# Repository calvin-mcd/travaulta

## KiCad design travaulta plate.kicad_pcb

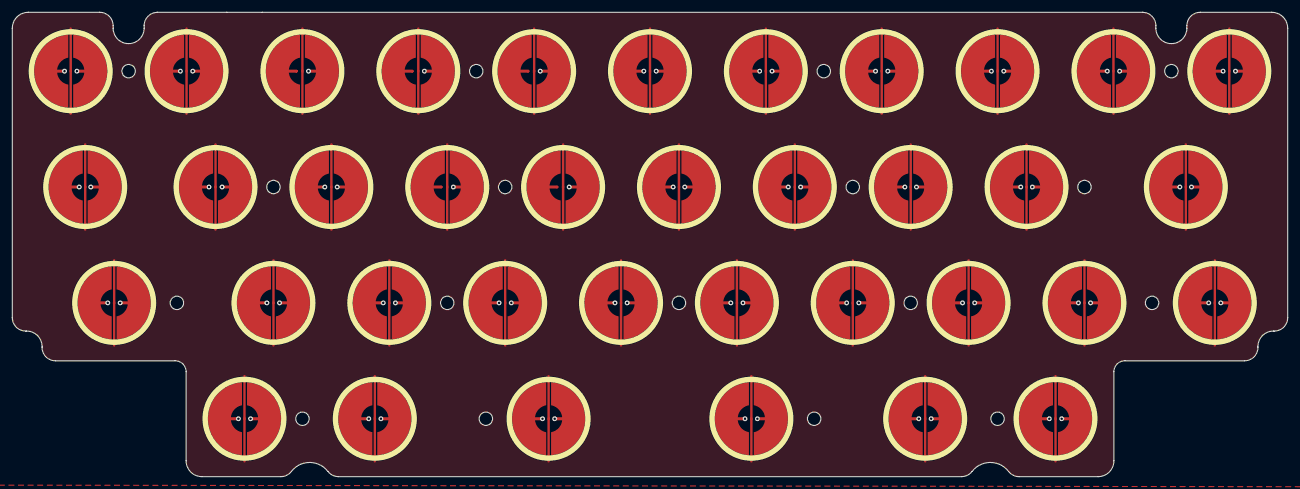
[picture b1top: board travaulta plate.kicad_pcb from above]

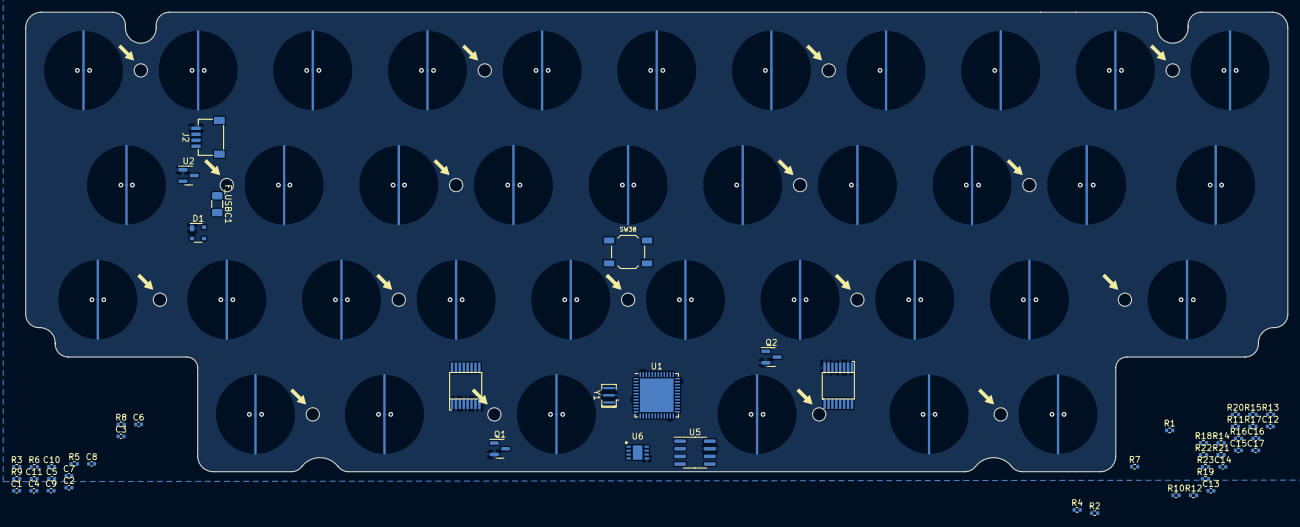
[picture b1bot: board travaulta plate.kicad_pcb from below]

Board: 4 copper layers, 209.7 x 76.4 mm, 116 parts (53 on the bottom side), 46 nets.

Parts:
C1, C2: 4.7u; C_0402_1005Metric
C3, C4, C5, C11, C17: 1u; C_0402_1005Metric
C6, C7, C8, C9, C10: 100n; C_0402_1005Metric
C12, C13, C15, C16: 0.1u; C_0402_1005Metric
C14: 220p; C_0402_1005Metric
D1: PRTR5V0U2X; SOT-143
F_USBC1: 500mA; Fuse_1206_3216Metric
H1, H2, H3, H4, H5, H6, H7, H8, H9, H10, H11, H12, H13, H14, H15, H16, H17, H18, H19, H20, H21, H22, H23, H24, H25, H26: MountingHole; HOLE_M2
J2: JST; JST-SR-4
Q1, Q2: 2N7002; SOT-23
R1, R2, R8, R9, R21: 100; R_0402_1005Metric
R3, R6, R7: 10k; R_0402_1005Metric
R4, R5, R10, R11, R12, R13, R14, R15, R16, R17, R18, R19, R20, R22: 100k; R_0402_1005Metric
R23: 1k; R_0402_1005Metric
SW1, SW2, SW3, SW4, SW5, SW6, SW7, SW8, SW9, SW10, SW11, SW12, SW13, SW14, SW15, SW16, SW17, SW18, SW19, SW20, SW21, SW22, SW23, SW24, SW25, SW26, SW27, SW28, SW29, SW30, SW31, SW32, SW33, SW34, SW35, SW36, SW37: EC_SW; ecs_pad_1U_no_ring
SW38: SW_MEC_5G; SW_SPST_TL3342
U1: STM32F411CCUx; QFN-48-1EP_7x7mm_P0.5mm_EP5.6x5.6mm
U2: XC6206PxxxMR; SOT-23
U3, U4: 74HC4051; TSSOP16
U5: OPA350; SOIC-8_3.9x4.9mm_P1.27mm
U6: MAX5423
Y1: 16 MHz; Resonator_SMD_Murata_CSTxExxV-3Pin_3.0x1.1mm

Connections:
+5V: C4.1, F_USBC1.2, U2.3 (VI)
ADC: U1.13 (PA3), U5.6 (OUT), U6.6 (L)
AMUX_SEL_0: U1.43 (PB7), U3.11 (S0), U4.11 (S0)
AMUX_SEL_1: U1.42 (PB6), U3.10 (S1), U4.10 (S1)
AMUX_SEL_2: U1.41 (PB5), U3.9 (S2), U4.9 (S2)
APLEX_EN_PIN_0: U1.46 (PB9), U4.6 (~E)
APLEX_EN_PIN_1: U1.45 (PB8), U3.6 (~E)
APLEX_OUT_PIN_0: C14.2, Q2.3 (D), U3.3 (A), U4.3 (A), U5.2 (IN-)
BOOT0: C2.1, R3.1, SW38.1 (A), SW38.2 (A), U1.44 (BOOT0)
BOOT1: R7.2, U1.20 (PB2)
COL0: R11.1, SW1.2, SW12.2, SW22.2, U4.13 (A0)
COL1: R13.1, SW2.2, SW13.2, SW23.2, SW32.2, U4.14 (A1)
COL2: R15.1, SW3.2, SW14.2, SW24.2, SW33.2, U4.15 (A2)
COL3: R17.1, SW4.2, SW15.2, SW25.2, SW34.2, U4.12 (A3)
COL4: R19.1, SW5.2, SW16.2, SW26.2, U4.1 (A4)
COL5: R20.1, SW6.2, SW17.2, SW27.2, SW35.2, U4.5 (A5)
COL6: R10.1, SW7.2, SW18.2, SW28.2, U3.13 (A0)
COL7: R12.1, SW8.2, SW19.2, SW29.2, SW36.2, U3.14 (A1)
COL8: R14.1, SW9.2, SW20.2, SW30.2, SW37.2, U3.15 (A2)
COL9: R16.1, SW10.2, SW21.2, SW31.2, U3.12 (A3)
COL10: R18.1, SW11.2, U3.1 (A4)
D+: D1.3 (I/O2), J2.3, U1.33 (PA12)
D-: D1.2 (I/O1), J2.2, U1.32 (PA11)
DISCHARGE_PIN: R21.1, U1.18 (PB0)
GND: C1.2, C3.2, C4.2, C5.2, C6.2, C7.2, C8.2, C9.2, C10.2, C11.2, C12.2, C13.2, C14.1, C15.2, C16.1, C17.1, D1.1 (GND), J2.4, Q1.2 (S), Q2.2 (S), R3.2, R5.2, R7.1, R10.2, R11.2, R12.2, R13.2, R14.2, R15.2, R16.2, R17.2, R18.2, R19.2, R20.2, R22.2, R23.2, SW1.3 (SG), SW2.3 (SG), SW3.3 (SG), SW4.3 (SG), SW5.3 (SG), SW6.3 (SG), SW7.3 (SG), SW8.3 (SG), SW9.3 (SG), SW10.3 (SG), SW11.3 (SG), SW12.3 (SG), SW13.3 (SG), SW14.3 (SG), SW15.3 (SG), SW16.3 (SG), SW17.3 (SG), SW18.3 (SG), SW19.3 (SG), SW20.3 (SG), SW21.3 (SG), SW22.3 (SG), SW23.3 (SG), SW24.3 (SG), SW25.3 (SG), SW26.3 (SG), SW27.3 (SG), SW28.3 (SG), SW29.3 (SG), SW30.3 (SG), SW31.3 (SG), SW32.3 (SG), SW33.3 (SG), SW34.3 (SG), SW35.3 (SG), SW36.3 (SG), SW37.3 (SG), U1.8 (VSSA), U1.23 (VSS), U1.35 (VSS), U1.47 (VSS), U1.49 (VSS), U2.1 (GND), U3.2 (A6), U3.4 (A7), U3.5 (A5), U3.7 (VEE), U3.8 (GND), U4.2 (A6), U4.4 (A7), U4.7 (VEE), U4.8 (GND), U5.7 (V+), U6.5 (Gnd), Y1.2
NRST: C3.1, Q1.3 (D), R6.2, U1.7 (NRST)
unnamed: C1.1, U1.22 (VCAP1)
unnamed: C2.2, Q1.1 (G), R5.1
unnamed: Q2.1 (G), R21.2, R22.1
unnamed: R1.1, U1.39 (PB3)
unnamed: R2.2, U1.40 (PB4)
unnamed: R4.1, U1.31 (PA10)
unnamed: R9.1, U1.38 (PA15)
RES_L: R23.1, U5.3 (IN+), U6.7 (W), U6.8 (H)
ROW0: R1.2, SW1.1, SW2.1, SW3.1, SW4.1, SW5.1, SW6.1, SW7.1, SW8.1, SW9.1, SW10.1, SW11.1
ROW1: R9.2, SW12.1, SW13.1, SW14.1, SW15.1, SW16.1, SW17.1, SW18.1, SW19.1, SW20.1, SW21.1
ROW2: R8.1, SW22.1, SW23.1, SW24.1, SW25.1, SW26.1, SW27.1, SW28.1, SW29.1, SW30.1, SW31.1
ROW3: R2.1, SW32.1, SW33.1, SW34.1, SW35.1, SW36.1, SW37.1
SPI1_CLK: U1.15 (PA5), U6.2 (SCLK)
SPI1_CS: U1.19 (PB1), U6.4 (CS)
SPI1_MOSI: U1.17 (PA7), U6.3 (Din)
SWCLK: R8.2, U1.37 (PA14)
VBAT: C5.1, C6.1, C7.1, C8.1, C9.1, C10.1, C11.1, C12.1, C13.1, C15.1, C16.2, C17.2, R4.2, R6.1, U1.1 (VBAT), U1.9 (VDDA), U1.24 (VDD), U1.36 (VDD), U1.48 (VDD), U2.2 (VO), U3.16 (VCC), U4.16 (VCC), U5.4 (V-), U6.1 (VCC)
VCC: D1.4 (VCC), F_USBC1.1, J2.1
XTAL0: U1.5 (PH0), Y1.3
XTAL1: U1.6 (PH1), Y1.1

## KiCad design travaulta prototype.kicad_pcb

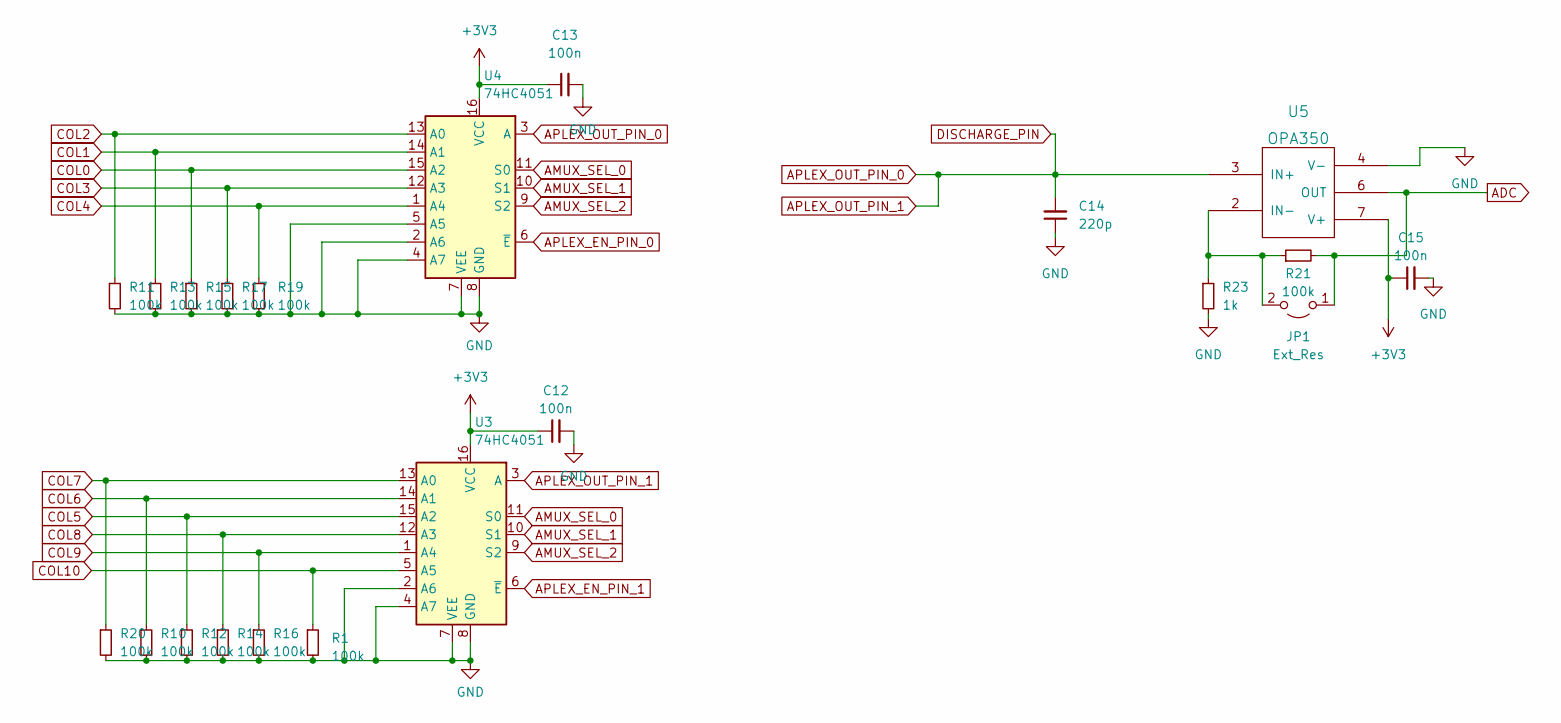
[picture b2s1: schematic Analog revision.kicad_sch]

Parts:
C12, C13, C15: 100n; C_0402_1005Metric
C14: 220p; C_0402_1005Metric
JP1: Ext_Res; R_0603_1608Metric_Pad0.98x0.95mm_HandSolder
R1, R10, R11, R12, R13, R14, R15, R16, R17, R19, R20, R21: 100k; R_0402_1005Metric
R23: 1k; R_0402_1005Metric
U3, U4: 74HC4051; TSSOP16
U5: OPA350; SOIC-8_3.9x4.9mm_P1.27mm

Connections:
ADC: JP1.1 (A), R21.2, U5.6 (OUT); also elsewhere on the board
AMUX_SEL_0: U3.11 (S0), U4.11 (S0); also elsewhere on the board
AMUX_SEL_1: U3.10 (S1), U4.10 (S1); also elsewhere on the board
AMUX_SEL_2: U3.9 (S2), U4.9 (S2); also elsewhere on the board
APLEX_EN_PIN_0: U4.6 (~E); also elsewhere on the board
APLEX_EN_PIN_1: U3.6 (~E); also elsewhere on the board
APLEX_OUT_PIN_0: C14.2, U3.3 (A), U4.3 (A), U5.3 (IN+); also elsewhere on the board
COL0: R15.1, U4.15 (A2); also elsewhere on the board
COL1: R13.1, U4.14 (A1); also elsewhere on the board
COL2: R11.1, U4.13 (A0); also elsewhere on the board
COL3: R17.1, U4.12 (A3); also elsewhere on the board
COL4: R19.1, U4.1 (A4); also elsewhere on the board
COL5: R12.1, U3.15 (A2); also elsewhere on the board
COL6: R10.1, U3.14 (A1); also elsewhere on the board
COL7: R20.1, U3.13 (A0); also elsewhere on the board
COL8: R14.1, U3.12 (A3); also elsewhere on the board
COL9: R16.1, U3.1 (A4); also elsewhere on the board
unnamed: JP1.2 (B), R21.1, R23.1, U5.2 (IN-)

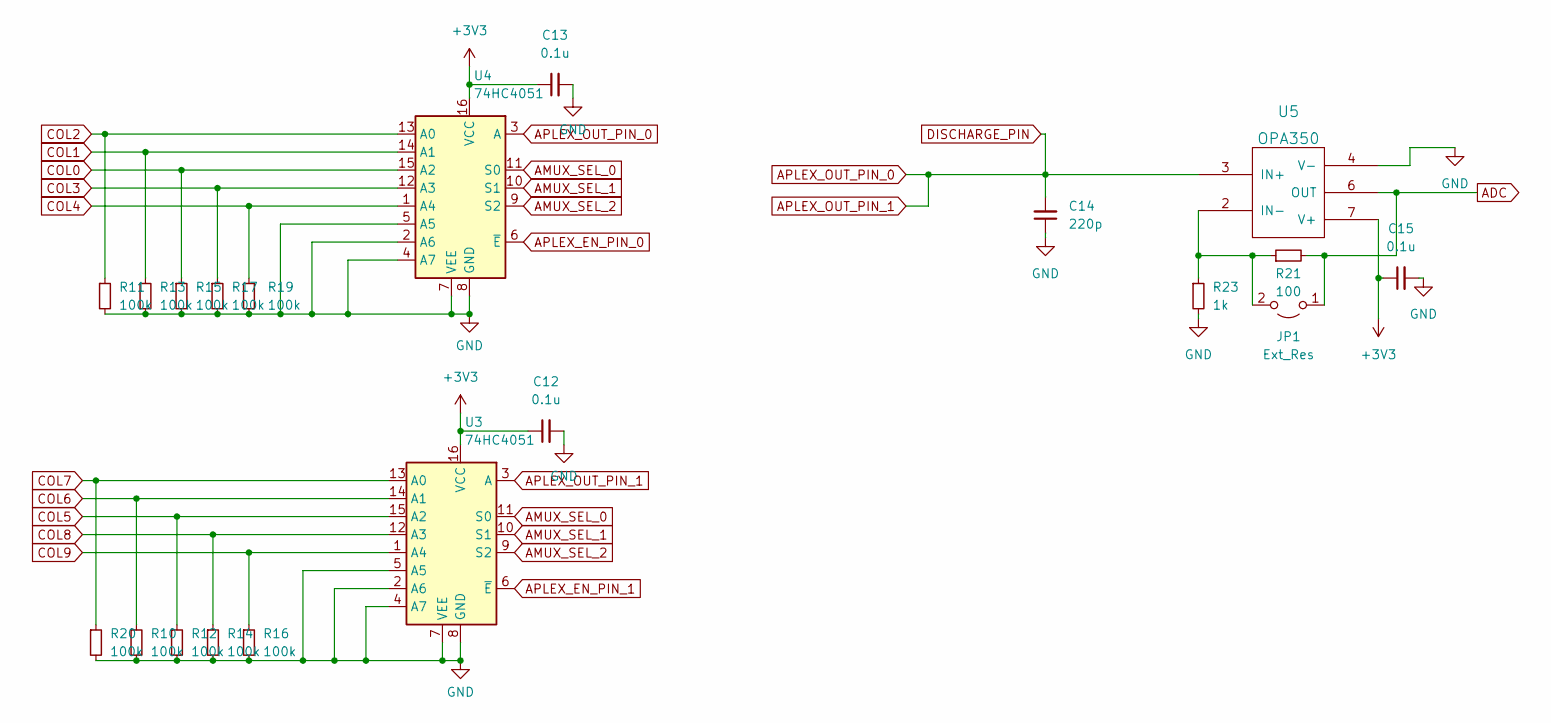
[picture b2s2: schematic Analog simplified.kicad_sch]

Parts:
C12, C13, C15: 0.1u; C_0402_1005Metric
C14: 220p; C_0402_1005Metric
JP1: Ext_Res; R_0603_1608Metric_Pad0.98x0.95mm_HandSolder
R10, R11, R12, R13, R14, R15, R16, R17, R19, R20: 100k; R_0402_1005Metric
R21: 100; R_0402_1005Metric
R23: 1k; R_0402_1005Metric
U3, U4: 74HC4051; TSSOP16
U5: OPA350; SOIC-8_3.9x4.9mm_P1.27mm

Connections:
ADC: JP1.1 (A), R21.2, U5.6 (OUT); also elsewhere on the board
AMUX_SEL_0: U3.11 (S0), U4.11 (S0); also elsewhere on the board
AMUX_SEL_1: U3.10 (S1), U4.10 (S1); also elsewhere on the board
AMUX_SEL_2: U3.9 (S2), U4.9 (S2); also elsewhere on the board
APLEX_EN_PIN_0: U4.6 (~E); also elsewhere on the board
APLEX_EN_PIN_1: U3.6 (~E); also elsewhere on the board
APLEX_OUT_PIN_0: C14.2, U3.3 (A), U4.3 (A), U5.3 (IN+); also elsewhere on the board
COL0: R15.1, U4.15 (A2); also elsewhere on the board
COL1: R13.1, U4.14 (A1); also elsewhere on the board
COL2: R11.1, U4.13 (A0); also elsewhere on the board
COL3: R17.1, U4.12 (A3); also elsewhere on the board
COL4: R19.1, U4.1 (A4); also elsewhere on the board
COL5: R12.1, U3.15 (A2); also elsewhere on the board
COL6: R10.1, U3.14 (A1); also elsewhere on the board
COL7: R20.1, U3.13 (A0); also elsewhere on the board
COL8: R14.1, U3.12 (A3); also elsewhere on the board
COL9: R16.1, U3.1 (A4); also elsewhere on the board
unnamed: JP1.2 (B), R21.1, R23.1, U5.2 (IN-)

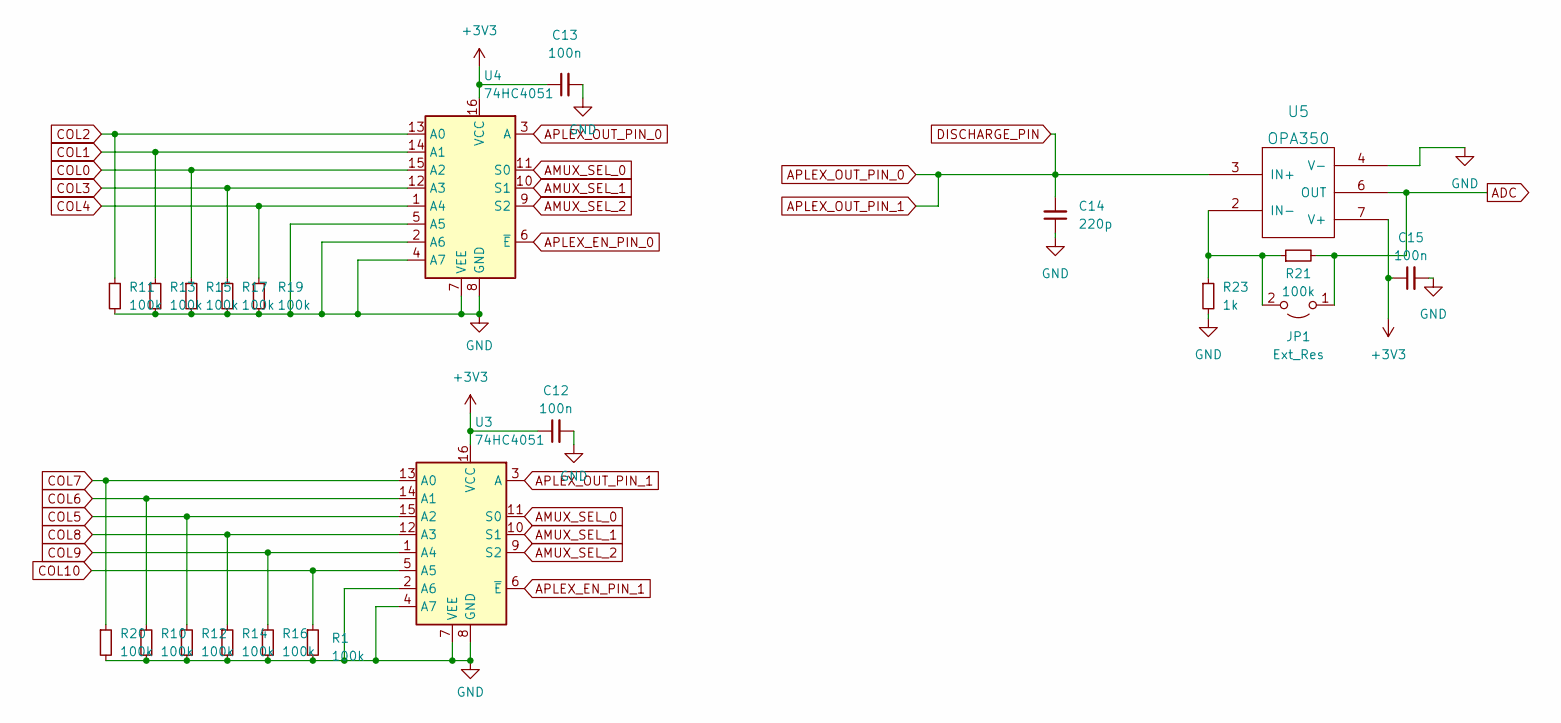
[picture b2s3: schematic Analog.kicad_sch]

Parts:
C12, C13, C15: 100n; C_0402_1005Metric
C14: 220p; C_0402_1005Metric
JP1: Ext_Res; R_0603_1608Metric_Pad0.98x0.95mm_HandSolder
R1, R10, R11, R12, R13, R14, R15, R16, R17, R19, R20, R21: 100k; R_0402_1005Metric
R23: 1k; R_0402_1005Metric
U3, U4: 74HC4051; TSSOP16
U5: OPA350; SOIC-8_3.9x4.9mm_P1.27mm

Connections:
ADC: JP1.1 (A), R21.2, U5.6 (OUT); also elsewhere on the board
AMUX_SEL_0: U3.11 (S0), U4.11 (S0); also elsewhere on the board
AMUX_SEL_1: U3.10 (S1), U4.10 (S1); also elsewhere on the board
AMUX_SEL_2: U3.9 (S2), U4.9 (S2); also elsewhere on the board
APLEX_EN_PIN_0: U4.6 (~E); also elsewhere on the board
APLEX_EN_PIN_1: U3.6 (~E); also elsewhere on the board
APLEX_OUT_PIN_0: C14.2, U3.3 (A), U4.3 (A), U5.3 (IN+); also elsewhere on the board
COL0: R15.1, U4.15 (A2); also elsewhere on the board
COL1: R13.1, U4.14 (A1); also elsewhere on the board
COL2: R11.1, U4.13 (A0); also elsewhere on the board
COL3: R17.1, U4.12 (A3); also elsewhere on the board
COL4: R19.1, U4.1 (A4); also elsewhere on the board
COL5: R12.1, U3.15 (A2); also elsewhere on the board
COL6: R10.1, U3.14 (A1); also elsewhere on the board
COL7: R20.1, U3.13 (A0); also elsewhere on the board
COL8: R14.1, U3.12 (A3); also elsewhere on the board
COL9: R16.1, U3.1 (A4); also elsewhere on the board
unnamed: JP1.2 (B), R21.1, R23.1, U5.2 (IN-)

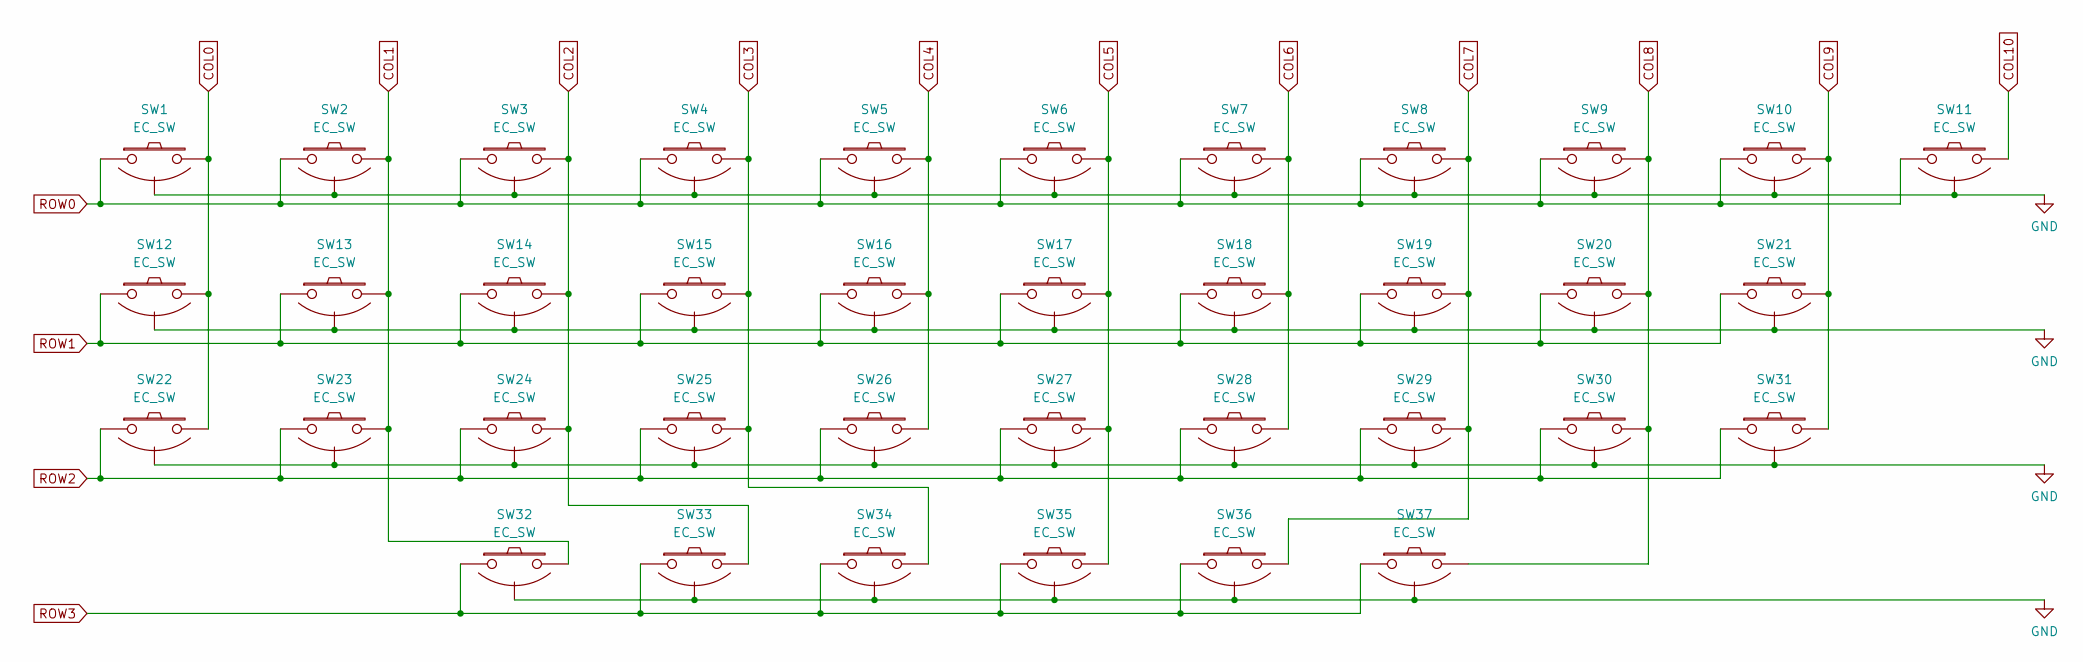
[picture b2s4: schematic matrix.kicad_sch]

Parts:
SW1, SW2, SW3, SW4, SW5, SW6, SW7, SW8, SW9, SW10, SW11, SW12, SW13, SW14, SW15, SW16, SW17, SW18, SW19, SW20, SW21, SW22, SW23, SW24, SW25, SW26, SW27, SW28, SW29, SW30, SW31, SW32, SW33, SW34, SW35, SW36, SW37: EC_SW; ecs_pad_1U_no_ring

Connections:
COL0: SW1.2, SW12.2, SW22.2; also elsewhere on the board
COL1: SW2.2, SW13.2, SW23.2, SW32.2; also elsewhere on the board
COL2: SW3.2, SW14.2, SW24.2, SW33.2; also elsewhere on the board
COL3: SW4.2, SW15.2, SW25.2, SW34.2; also elsewhere on the board
COL4: SW5.2, SW16.2, SW26.2; also elsewhere on the board
COL5: SW6.2, SW17.2, SW27.2, SW35.2; also elsewhere on the board
COL6: SW7.2, SW18.2, SW28.2; also elsewhere on the board
COL7: SW8.2, SW19.2, SW29.2, SW36.2; also elsewhere on the board
COL8: SW9.2, SW20.2, SW30.2, SW37.2; also elsewhere on the board
COL9: SW10.2, SW21.2, SW31.2; also elsewhere on the board
ROW0: SW1.1, SW2.1, SW3.1, SW4.1, SW5.1, SW6.1, SW7.1, SW8.1, SW9.1, SW10.1, SW11.1; also elsewhere on the board
ROW1: SW12.1, SW13.1, SW14.1, SW15.1, SW16.1, SW17.1, SW18.1, SW19.1, SW20.1, SW21.1; also elsewhere on the board
ROW2: SW22.1, SW23.1, SW24.1, SW25.1, SW26.1, SW27.1, SW28.1, SW29.1, SW30.1, SW31.1; also elsewhere on the board

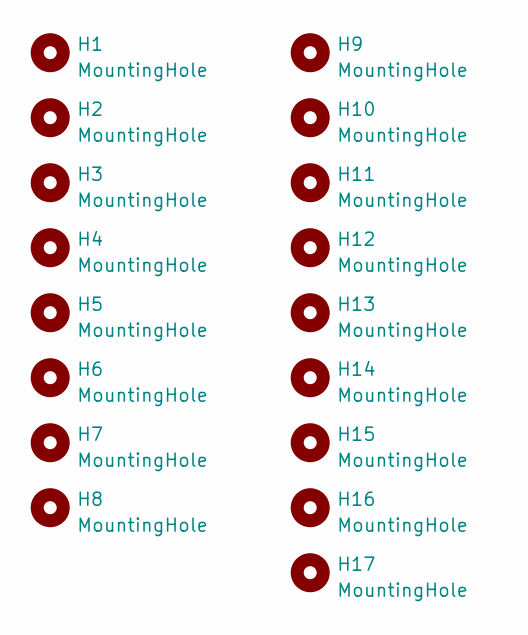
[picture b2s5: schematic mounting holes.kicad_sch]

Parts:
H1, H2, H3, H4, H5, H6, H7, H8, H9, H10, H11, H12, H13, H14, H15, H16, H17: MountingHole; HOLE_M2

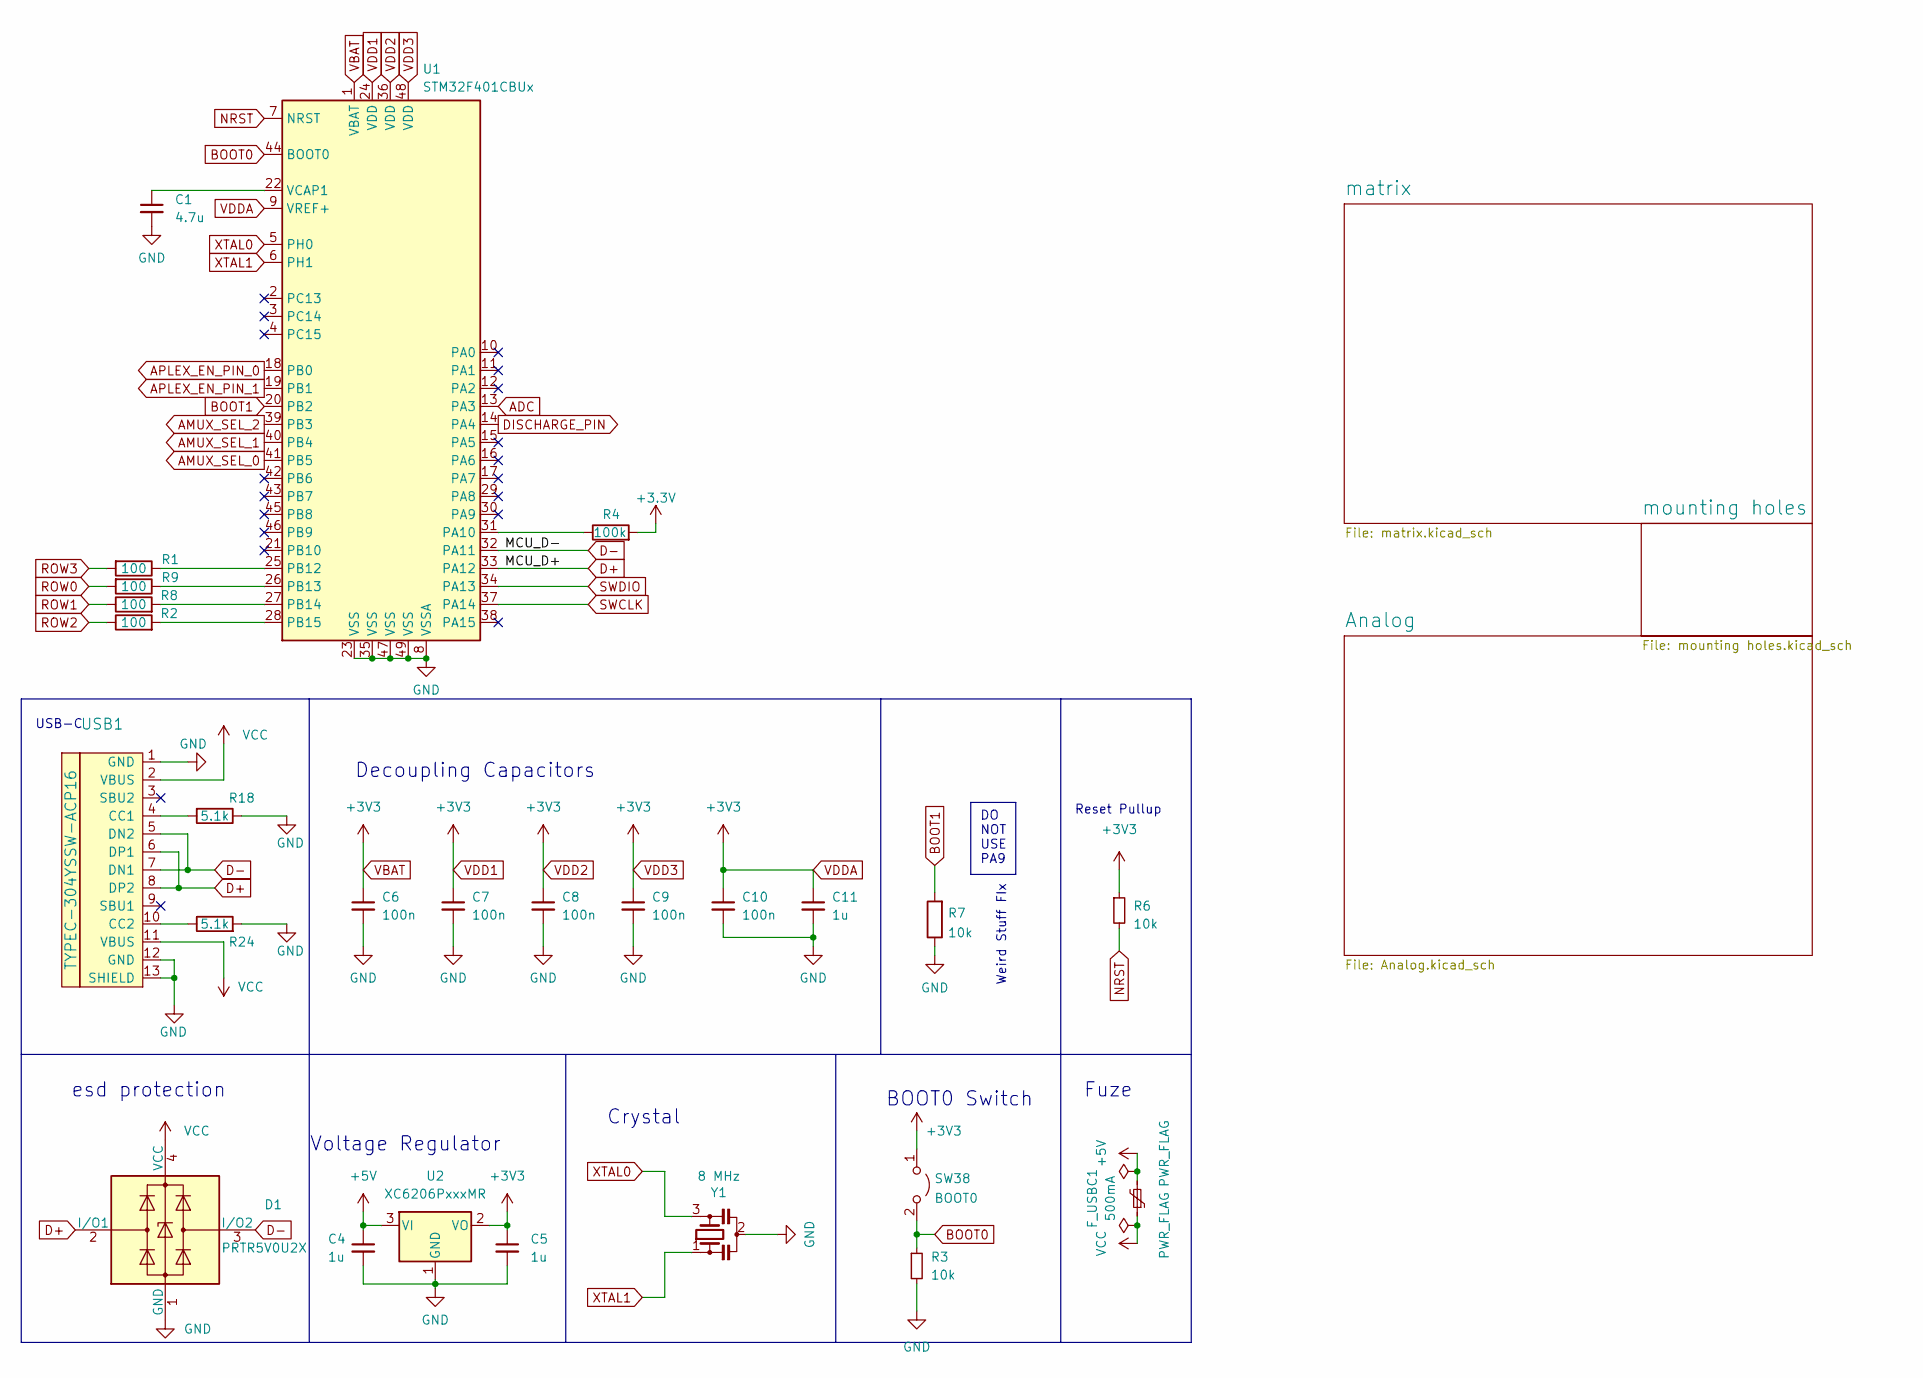
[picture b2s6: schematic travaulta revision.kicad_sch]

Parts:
C1: 4.7u; C_0402_1005Metric
C4, C5, C11: 1u; C_0402_1005Metric
C6, C7, C8, C9, C10: 100n; C_0402_1005Metric
D1: PRTR5V0U2X; SOT-143
F_USBC1: 500mA; Fuse_1206_3216Metric
R1, R2, R8, R9: 100; R_0402_1005Metric; LCSC C25076
R3, R6: 10k; R_0402_1005Metric
R4: 100k; R_0402_1005Metric; LCSC C25741
R7: 10k; R_0402_1005Metric; LCSC C25744
R18, R24: 5.1k; R_0402_1005Metric; LCSC C25905
SW38: BOOT0; PinHeader_1x02_P2.54mm_Vertical
U1: STM32F401CBUx; QFN-48-1EP_7x7mm_P0.5mm_EP5.6x5.6mm; LCSC C118825
U2: XC6206PxxxMR; SOT-23
USB1: TYPEC-304YSSW-ACP16; LCSC C2840392
Y1: 8 MHz; Resonator_SMD_Murata_CSTxExxV-3Pin_3.0x1.1mm; LCSC C907975

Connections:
+5V: C4.1, F_USBC1.2, U2.3 (VI)
ADC: U1.13 (PA3); also elsewhere on the board
AMUX_SEL_0: U1.41 (PB5); also elsewhere on the board
AMUX_SEL_1: U1.40 (PB4); also elsewhere on the board
AMUX_SEL_2: U1.39 (PB3); also elsewhere on the board
APLEX_EN_PIN_0: U1.18 (PB0); also elsewhere on the board
APLEX_EN_PIN_1: U1.19 (PB1); also elsewhere on the board
APLEX_OUT_PIN_0: U1.14 (PA4); also elsewhere on the board
BOOT0: R3.1, SW38.2 (B), U1.44 (BOOT0)
BOOT1: R7.2, U1.20 (PB2)
D+: D1.2 (I/O1), U1.33 (PA12), USB1.6 (DP1), USB1.8 (DP2)
D-: D1.3 (I/O2), U1.32 (PA11), USB1.5 (DN2), USB1.7 (DN1)
NRST: R6.2, U1.7 (NRST)
unnamed: R4.1, U1.31 (PA10)
unnamed: R9.1, U1.26 (PB13)
unnamed: R8.2, U1.27 (PB14)
unnamed: R2.2, U1.28 (PB15)
unnamed: C1.1, U1.22 (VCAP1)
unnamed: R18.2, USB1.4 (CC1)
unnamed: R24.1, USB1.10 (CC2)
ROW0: R9.2; also elsewhere on the board
ROW1: R8.1; also elsewhere on the board
ROW2: R2.1; also elsewhere on the board
SWCLK: U1.37 (PA14)
SWDIO: U1.34 (PA13)
VCC: D1.4 (VCC), F_USBC1.1, USB1.2 (VBUS), USB1.11 (VBUS)
XTAL0: U1.5 (PH0), Y1.3
XTAL1: U1.6 (PH1), Y1.1

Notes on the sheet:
Weird Stuff FIx
BOOT0 Switch
USB-C
Voltage Regulator
Reset Pullup
esd protection
DO NOT USE PA9
Fuze
Crystal
Decoupling Capacitors

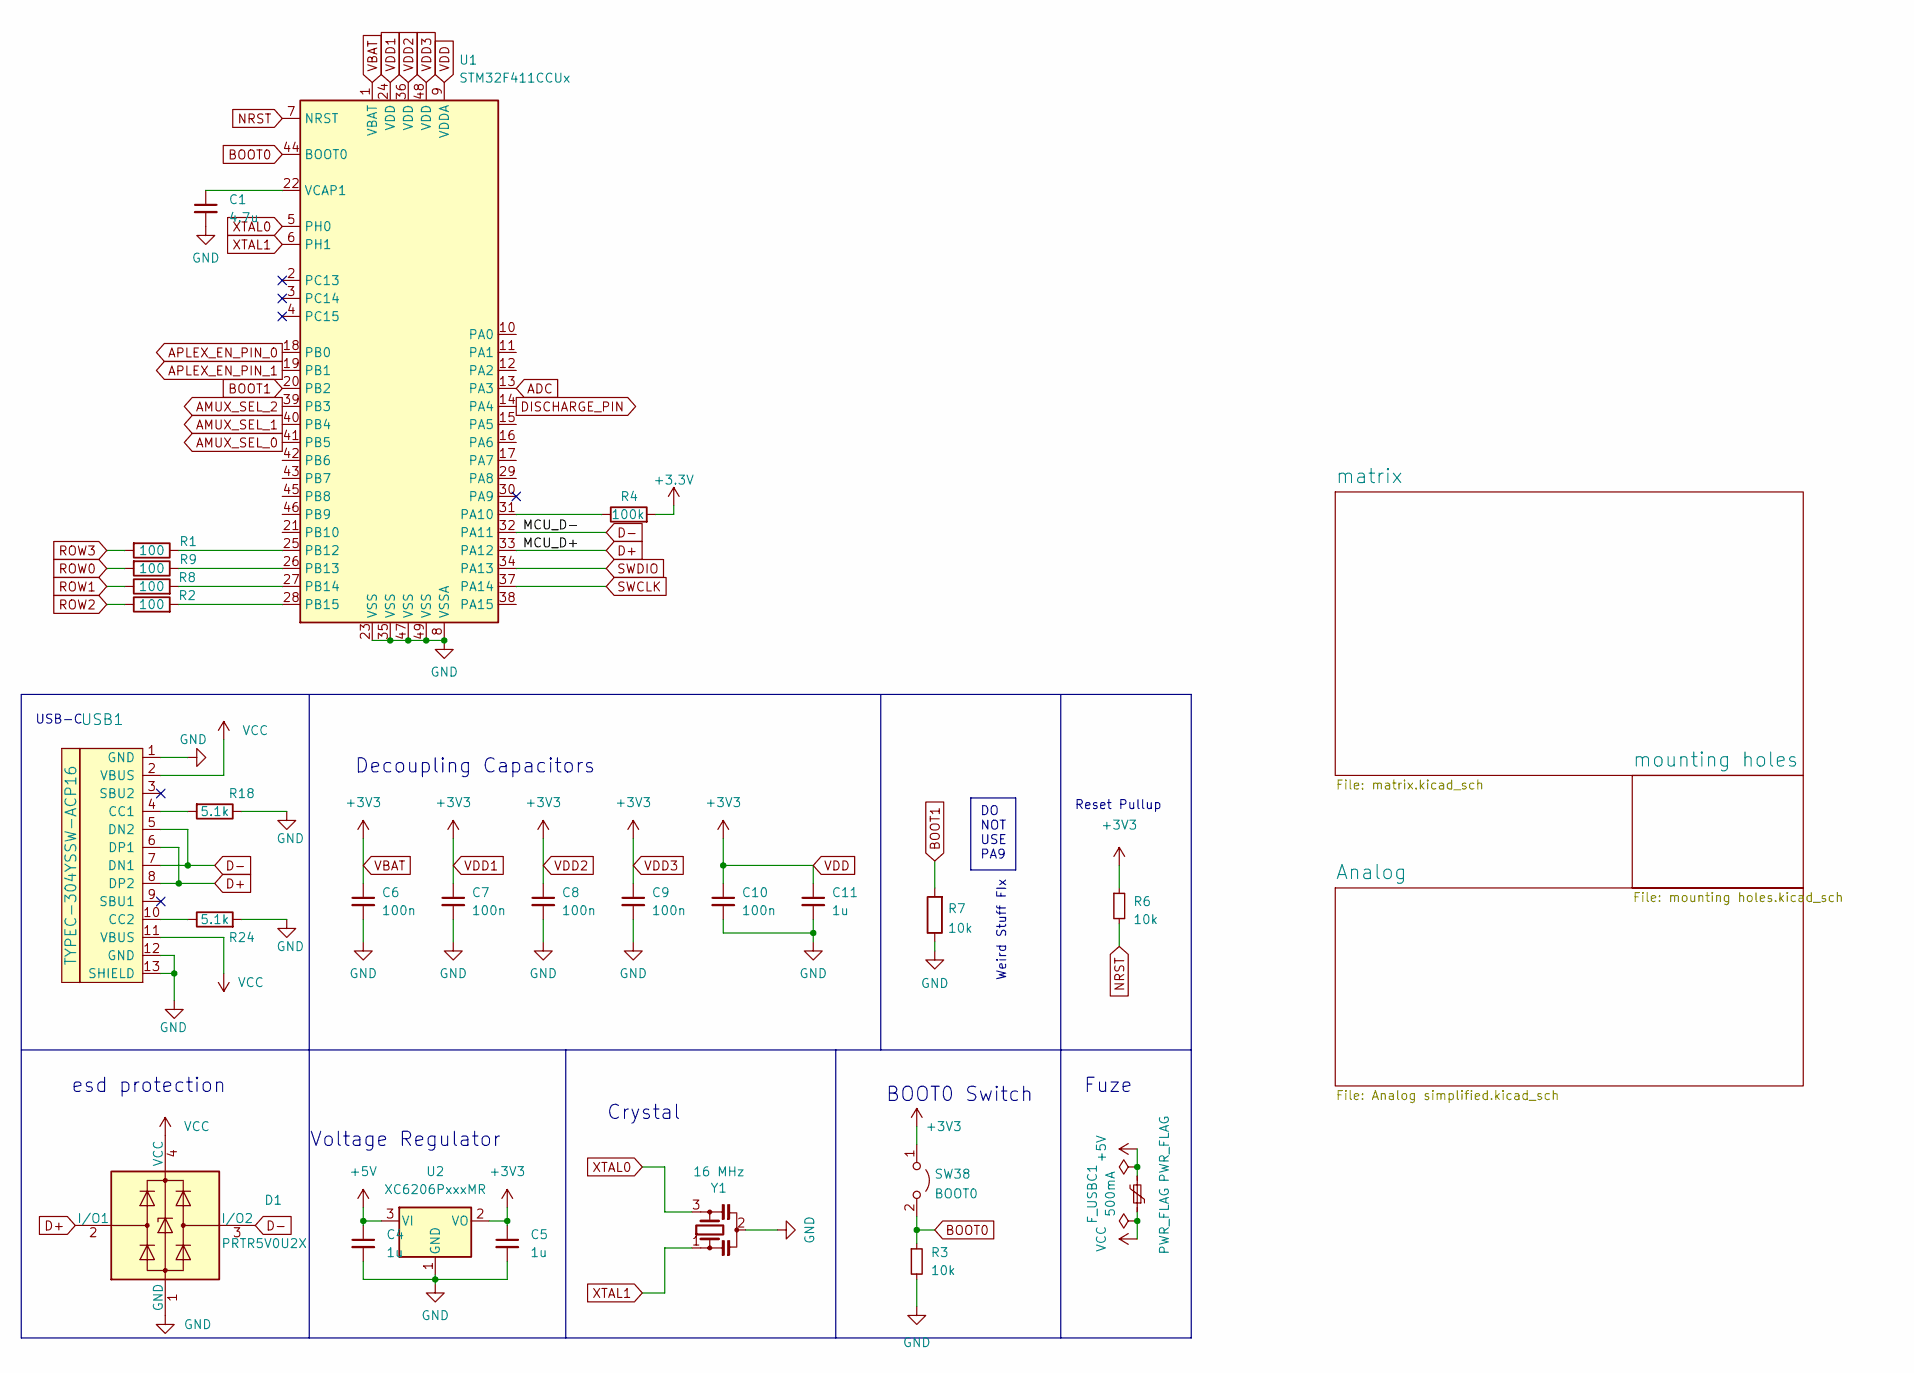
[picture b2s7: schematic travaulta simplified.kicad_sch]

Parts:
C1: 4.7u; C_0402_1005Metric
C4, C5, C11: 1u; C_0402_1005Metric
C6, C7, C8, C9, C10: 100n; C_0402_1005Metric
D1: PRTR5V0U2X; SOT-143
F_USBC1: 500mA; Fuse_1206_3216Metric
R1, R2, R8, R9: 100; R_0402_1005Metric; LCSC C25076
R3, R6: 10k; R_0402_1005Metric
R4: 100k; R_0402_1005Metric; LCSC C25741
R7: 10k; R_0402_1005Metric; LCSC C25744
R18, R24: 5.1k; R_0402_1005Metric; LCSC C25905
SW38: BOOT0; PinHeader_1x02_P2.54mm_Vertical
U1: STM32F411CCUx; QFN-48-1EP_7x7mm_P0.5mm_EP5.6x5.6mm
U2: XC6206PxxxMR; SOT-23
USB1: TYPEC-304YSSW-ACP16; LCSC C2840392
Y1: 16 MHz; Resonator_SMD_Murata_CSTxExxV-3Pin_3.0x1.1mm; LCSC C907975

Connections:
+5V: C4.1, F_USBC1.2, U2.3 (VI)
ADC: U1.13 (PA3); also elsewhere on the board
AMUX_SEL_0: U1.41 (PB5); also elsewhere on the board
AMUX_SEL_1: U1.40 (PB4); also elsewhere on the board
AMUX_SEL_2: U1.39 (PB3); also elsewhere on the board
APLEX_EN_PIN_0: U1.18 (PB0); also elsewhere on the board
APLEX_EN_PIN_1: U1.19 (PB1); also elsewhere on the board
APLEX_OUT_PIN_0: U1.14 (PA4); also elsewhere on the board
BOOT0: R3.1, SW38.2 (B), U1.44 (BOOT0)
BOOT1: R7.2, U1.20 (PB2)
D+: D1.2 (I/O1), U1.33 (PA12), USB1.6 (DP1), USB1.8 (DP2)
D-: D1.3 (I/O2), U1.32 (PA11), USB1.5 (DN2), USB1.7 (DN1)
NRST: R6.2, U1.7 (NRST)
unnamed: R4.1, U1.31 (PA10)
unnamed: R9.1, U1.26 (PB13)
unnamed: R8.2, U1.27 (PB14)
unnamed: R2.2, U1.28 (PB15)
unnamed: C1.1, U1.22 (VCAP1)
unnamed: R18.2, USB1.4 (CC1)
unnamed: R24.1, USB1.10 (CC2)
ROW0: R9.2; also elsewhere on the board
ROW1: R8.1; also elsewhere on the board
ROW2: R2.1; also elsewhere on the board
SWCLK: U1.37 (PA14)
SWDIO: U1.34 (PA13)
VCC: D1.4 (VCC), F_USBC1.1, USB1.2 (VBUS), USB1.11 (VBUS)
XTAL0: U1.5 (PH0), Y1.3
XTAL1: U1.6 (PH1), Y1.1

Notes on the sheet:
Weird Stuff FIx
BOOT0 Switch
USB-C
Voltage Regulator
Reset Pullup
esd protection
DO NOT USE PA9
Fuze
Crystal
Decoupling Capacitors
